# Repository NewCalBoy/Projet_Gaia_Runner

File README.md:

# Projet Gaïa Runner
Projet de 2ème année 2025 by SERAPHIN Bradley et DAVERAT Arthur

## Description du projet
Le projet consiste a créer un petit robot de type rover avec un bras articulé. La particularité du projet est qu'il est à architecture déporté, c'est-à-dire que le contrôle des roues est gérée par un microcontrôleur, autre que le microcontrôleur principal.

Voici ci-joint un exemple de rover avec un bras articulé.

Dans un premier temps nous réaliserons d'abord le châssis, puis nous réaliserons dans un second temps la pince.

## Différentes parties
### Partie 1 : Rover
### Partie 2 : Bras robotisé
### Partie 3 : Pilotage
## Présentation
Lien de la présentation : https://www.canva.com/design/DAG3vKNjyPE/KJl2cilKYN6kFEWi7G_Mkw/edit?utm_content=DAG3vKNjyPE&utm_campaign=designshare&utm_medium=link2&utm_source=sharebutton

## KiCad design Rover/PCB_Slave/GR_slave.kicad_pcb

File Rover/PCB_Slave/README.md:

# PCB Esclave

## Description
Voici le PCB Esclave qui a pour but de gérer la commande des moteurs DC.

Il y a 4 composants principaux : le microcontrolleur, le pont H, le LDO et l'optocoupleur.
Nous avons également 4 connecteurs JST : deux JST pour  l'I2C, un jst pour l'alimentation et un pour le moteur.

## Fonctionnement
### Etape 1
Le PCB Maître communique un octet avec le PCB Esclave via I2C. 
En fonction de la combinaisons des jumpers, l'adresse I2C du PCB Esclave est différente plus de détails dans la section [Adressage I2C]().
### Etape 2
En fonction de l'octet reçu, le PCB Esclave sait s'il doit avancer ou reculer et la vitesse attendue.

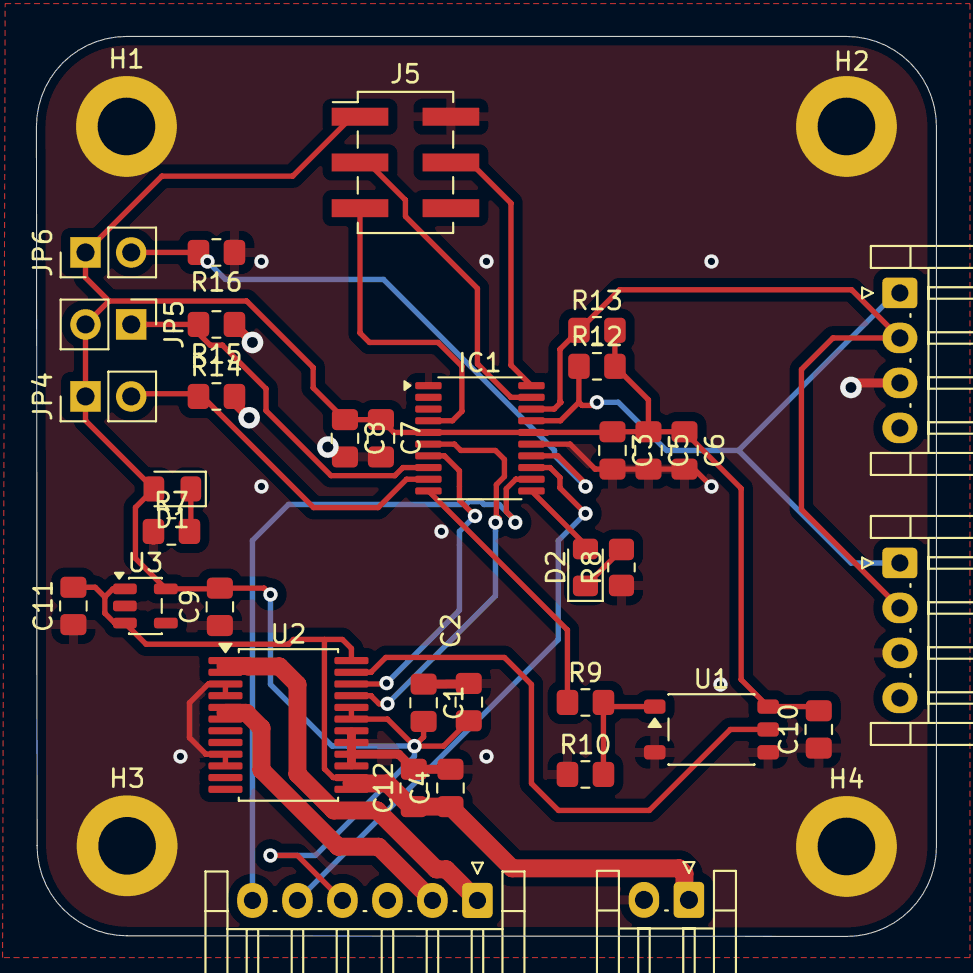
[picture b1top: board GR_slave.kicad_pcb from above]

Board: 2 copper layers, 50.0 x 50.0 mm, 39 parts (0 on the bottom side), 23 nets.

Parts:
C1, C12: 0.1u; C_0805_2012Metric_Pad1.18x1.45mm_HandSolder
C2, C4: 10u; C_0805_2012Metric_Pad1.18x1.45mm_HandSolder
C3: 4.7u; C_0805_2012Metric_Pad1.18x1.45mm_HandSolder
C5, C6: 100n; C_0805_2012Metric_Pad1.18x1.45mm_HandSolder
C7: 10n; C_0805_2012Metric_Pad1.18x1.45mm_HandSolder
C8: 1u; C_0805_2012Metric_Pad1.18x1.45mm_HandSolder
C9, C11: 1uF; C_0805_2012Metric_Pad1.18x1.45mm_HandSolder
C10: 0.1uF; C_0805_2012Metric_Pad1.18x1.45mm_HandSolder
D1, D2: LED; LED_0805_2012Metric_Pad1.15x1.40mm_HandSolder
H1, H2, H3, H4: MountingHole_Pad; MountingHole_3.2mm_M3_DIN965_Pad
IC1: STM32F030F4P6; TSSOP-20_4.4x6.5mm_P0.65mm
J2: Conn_01x02; JST_EH_S2B-EH_1x02_P2.50mm_Horizontal
J3, J4: Conn_01x04; JST_EH_S4B-EH_1x04_P2.50mm_Horizontal
J5: T821106A1S100CEU; PinHeader_2x03_P2.54mm_Vertical_SMD
J6: Conn_01x06; JST_EH_S6B-EH_1x06_P2.50mm_Horizontal
JP4, JP5, JP6: Jumper_2_Open; PinHeader_1x02_P2.54mm_Vertical
R7, R8: 270; R_0805_2012Metric_Pad1.20x1.40mm_HandSolder
R9, R10: 210; R_0805_2012Metric_Pad1.20x1.40mm_HandSolder
R12, R13: 4.7k; R_0805_2012Metric_Pad1.20x1.40mm_HandSolder
R14, R15, R16: 10k; R_0805_2012Metric_Pad1.20x1.40mm_HandSolder
U1: TLP2361; SO-5-6_4.55x3.7mm_P1.27mm
U2: TB6612FNG; SSOP-24_5.3x8.2mm_P0.65mm
U3: MIC5219-3.3YM5; SOT-23-5

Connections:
+3.3V: C1.2, C2.1, C3.1, C5.1, C6.1, C7.1, C8.1, C9.2, C10.2, D1.2 (A), IC1.5 (VDDA), IC1.16 (VDD), J5.1, J6.4, JP4.1 (A), JP5.2 (B), JP6.1 (A), R12.2, R13.2, U1.6, U2.19 (STBY), U2.20 (VCC), U3.5 (OUT)
+12V: C4.1, C11.2, C12.1, J2.1, U2.13 (VM2), U2.14 (VM3), U2.24 (VM1), U3.1 (IN), U3.3 (EN)
AIN1: IC1.6 (PA0), U2.21 (AIN1)
AIN2: IC1.7 (PA1), U2.22 (AIN2)
AO1: J6.1, U2.1 (AO1), U2.2 (AO1)
AO2: J6.2, U2.5 (AO2), U2.6 (AO2)
GND: C1.1, C2.2, C3.2, C4.2, C5.2, C6.2, C7.2, C8.2, C9.1, C10.1, C11.1, C12.2, H1.1, H2.1, H3.1, H4.1, IC1.1 (BOOT0), IC1.15 (VSS), J2.2, J3.3, J4.3, J5.2, J6.3, R7.1, R8.1, R10.1, R14.2, R15.1, R16.1, U1.3, U1.4, U2.3 (PGND1), U2.4 (PGND1), U2.9 (PGND2), U2.10 (PGND2), U2.15 (PWMB), U2.16 (BIN2), U2.17 (BIN1), U2.18 (GND), U3.2 (GND)
LED: D2.2 (A), IC1.11 (PA5)
NRST: IC1.4 (NRST), J5.5
unnamed: D1.1 (K), R7.2
unnamed: D2.1 (K), R8.2
unnamed: IC1.8 (PA2), JP5.1 (A), R15.2
unnamed: IC1.9 (PA3), JP4.2 (B), R14.1
unnamed: IC1.14 (PB1), JP6.2 (B), R16.2
unnamed: R9.2, R10.2, U1.1
PWM H-bridge: U1.5, U2.23 (PWMA)
PWM MCU: IC1.10 (PA4), R9.1
SCL: IC1.17 (PA9), J3.1, J4.1, R12.1
SDA: IC1.18 (PA10), J3.2, J4.2, R13.1
SENSOR A ENCODEUR: IC1.13 (PA7), J6.5
SENSOR B ENCODEUR: IC1.12 (PA6), J6.6
SWCLK: IC1.20 (PA14), J5.4
SWDIO: IC1.19 (PA13), J5.3

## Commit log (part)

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2025-11-25 Rename Présentation du projet.md to Presentation_du_projet.md
2026-01-13 Update project description in README
    Clarified the architecture of the rover project.
2026-01-13 Update figure caption format in README
2026-01-13 Update figure caption formatting in README
2026-01-13 Fix link format in README for DC motor section
    Corrected the link format for the DC motor section.
2026-01-13 Fix formatting and punctuation in README.md
2026-01-13 Fix formatting in README.md for motor details
2026-01-13 Update README with technical solutions and details
    Added details about omnidirectional wheels and slave PCBs.
2026-01-13 Update README with new image and video example
    Added a new image and a video example section to the README.
2026-01-13 Change image link to relative path
    Updated the image link to a relative path in the README.
2026-01-13 Change image reference to markdown link format
    Updated image reference format in project description.
2026-01-13 Fix image link formatting in README
    Updated image link format in the project description.
2026-01-13 Update image link in README
    Fix image link formatting in project description.
2026-02-03 Modify image dimensions in README.md
    Updated image size in the PCB Slave README.
2026-02-03 Add image to PCB Slave README
    Added an image to the PCB Slave README for better visualization.
2026-02-03 Enhance PCB Slave README with image and formatting
    Updated the README to include an image and improved formatting.
2026-02-03 Update README with new PCB Slave image
    Added a new image to the README for PCB Slave.
2026-02-03 Fix image source path in PCB Slave README
    Updated image source path in README for PCB Slave.
2026-02-03 Fix image tag in PCB Slave README
2026-02-03 Update README with I2C communication details
    Added a new section about I2C communication and addressing.
2026-02-03 Update README with details on components and connectors
    Added information about main components and connectors.
2026-02-03 Update image path in PCB Slave README
